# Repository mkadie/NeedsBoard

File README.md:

# T-Rex Talk — AAC Communication Device

An open-source Augmentative and Alternative Communication (AAC) device
that helps people communicate by pressing pictures on a screen. When a
picture is pressed, the device speaks a word or phrase out loud.

**No programming knowledge needed.** Teachers and parents customize
the device by editing simple text files.

*Four T-Rex Talk devices in custom 3D printed cases — touch screen and encoder variants*

<table>
<tr>
<td><br><em>Button + LCD variant</em></td>
<td><br><em>Picture button variant</em></td>
</tr>
</table>

> **Build your own!** See the [Build-a-Box photo album](https://photos.app.goo.gl/G9FtMMnnMuZ1zZxx8) for step-by-step 3D printing and assembly photos.

## Quick Start

1. **Flash CircuitPython** onto a supported device ([SETUP.md](SETUP.md))
2. **Copy the installer** to an SD card ([installer/README.md](installer/README.md))
3. **Insert SD card and reboot** — auto-configures everything
4. **Customize** menus and sounds ([GUIDE_FOR_TEACHERS.md](GUIDE_FOR_TEACHERS.md))

## Supported Devices

| Device | Screen | Input | Best For |
|--------|--------|-------|----------|
| **CYD_PLUS** | 320×240 color touch | Touch screen | Primary AAC device |
| **Fruit Jam** | 160×128 color LCD | Rotary encoder | Compact, low-power |
| **OLED Badge** | 128×32 mono OLED | Rotary encoder | Wearable, text-only |
| **Feather RP2350** | 320×240 color LCD | 8 physical buttons + encoder | Physical button access |

## Features

- **Picture-based communication** — touch or press to speak
- **Menu system** — organize vocabulary into topic boards
- **Emergency button** — instant help message on hold (~1.2 seconds)
- **Configurable** — volume, speed, sleep, encoder direction via config.txt
- **Multi-language** — bilingual support (tested with Thai/English)
- **Playback speed** — slow down speech for pre-verbal learners
- **Sleep/wake** — battery-friendly power management
- **SD card installer** — auto-detects board and configures device

## Documentation

| Document | Audience |
|----------|----------|
| [SETUP.md](SETUP.md) | Setting up a new device |
| [GUIDE_FOR_TEACHERS.md](GUIDE_FOR_TEACHERS.md) | Teachers and parents — customizing menus and sounds |
| [user_manual/USER_MANUAL.html](user_manual/USER_MANUAL.html) | End users — daily operation guide |
| [menu_system.md](menu_system.md) | Technical — menu file format reference |
| [HISTORY.md](HISTORY.md) | Project version history |
| [NOTES.md](NOTES.md) | Development notes and future plans |
| [Credits.md](Credits.md) | Contributors and acknowledgments |
Link to google docs schedule of events https://docs.google.com/document/d/1B_Ffg2c_vWS-k63qlIgnEBgbQ5qvtrQ6X7UFEZSzED0/edit?usp=sharing

## Project Structure

```
code.py                 ← Entry point
machine.py              ← Main orchestrator
hardware_config.py      ← Device variant definitions
config.txt              ← User settings (per device)
display_manager.py      ← Display drivers (ILI9341, ST7735R, SSD1306)
audio_player.py         ← MP3/WAV playback with speed control
input_manager.py        ← Touch, encoder, I2C buttons
sleep_manager.py        ← Power management
menu_parser.py          ← .menu file reader
action.py               ← Press actions (sound, image, vibrate, navigate)
config_reader.py        ← config.txt parser
storage_manager.py      ← SD card support

menus/                  ← Menu definitions (.menu files)
    images/             ← Button images
    sounds/             ← Sound files
button_sounds/          ← Base menu sounds
installer/              ← SD card auto-installer
user_manual/            ← HTML user manual with images
original_icons/         ← Source icon library
```

## Configuration (config.txt)

```
volume = 80
playback_speed = 100
sleep_timeout = 120
start_menu = base.menu
emergency_push_enabled = true
encoder_direction_flip = false
```

See [GUIDE_FOR_TEACHERS.md](GUIDE_FOR_TEACHERS.md) for all settings.

## Contributing

See [help_wanted.md](help_wanted.md) for ways to contribute:
- Software engineers
- 3D designers
- Special needs experts
- Symbol/icon designers
- Web developers

## License

MIT License — see [LICENSE](LICENSE)

## Project History

This project began in the early 1990s when Michael Kadie built two speech
boards for children with special needs.

*The original speech boards (1990s) — inspiration for T-Rex Talk*

See [HISTORY.md](HISTORY.md) for the full version history from V0.x to V3.0.

## Credits

Created by Michael Kadie. See [Credits.md](Credits.md) for full acknowledgments.

---

*T-Rex Talk: Giving a voice to those who need one.*

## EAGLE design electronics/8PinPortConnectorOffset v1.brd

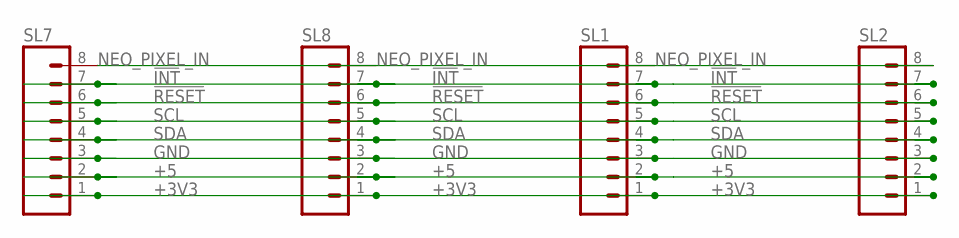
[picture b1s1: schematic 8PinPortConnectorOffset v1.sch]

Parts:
SL1, SL2, SL7, SL8: MA08; 08PA

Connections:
!INT: SL1.7, SL2.7, SL7.7, SL8.7
!RESET: SL1.6, SL2.6, SL7.6, SL8.6
+3V3: SL1.1, SL2.1, SL7.1, SL8.1
+5: SL1.2, SL2.2, SL7.2, SL8.2
GND: SL1.3, SL2.3, SL7.3, SL8.3
NEO_PIXEL_IN: SL1.8, SL2.8, SL7.8, SL8.8
SCL: SL1.5, SL2.5, SL7.5, SL8.5
SDA: SL1.4, SL2.4, SL7.4, SL8.4

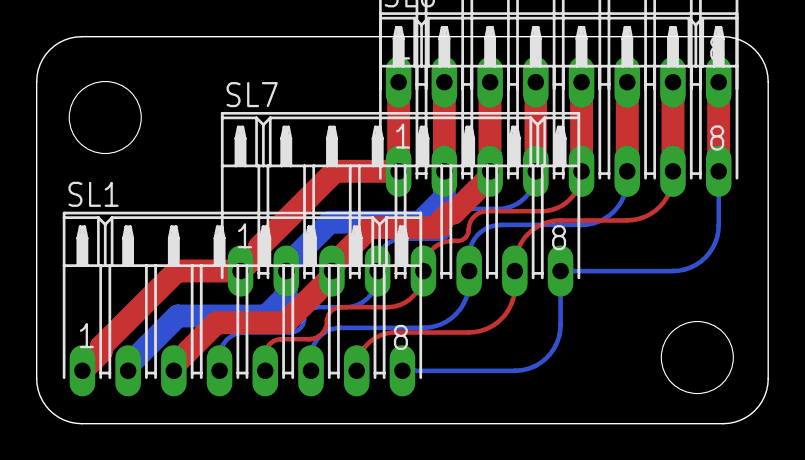
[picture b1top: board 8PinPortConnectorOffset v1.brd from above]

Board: 2 copper layers, 40.6 x 21.5 mm, 4 parts (0 on the bottom side), 8 nets.

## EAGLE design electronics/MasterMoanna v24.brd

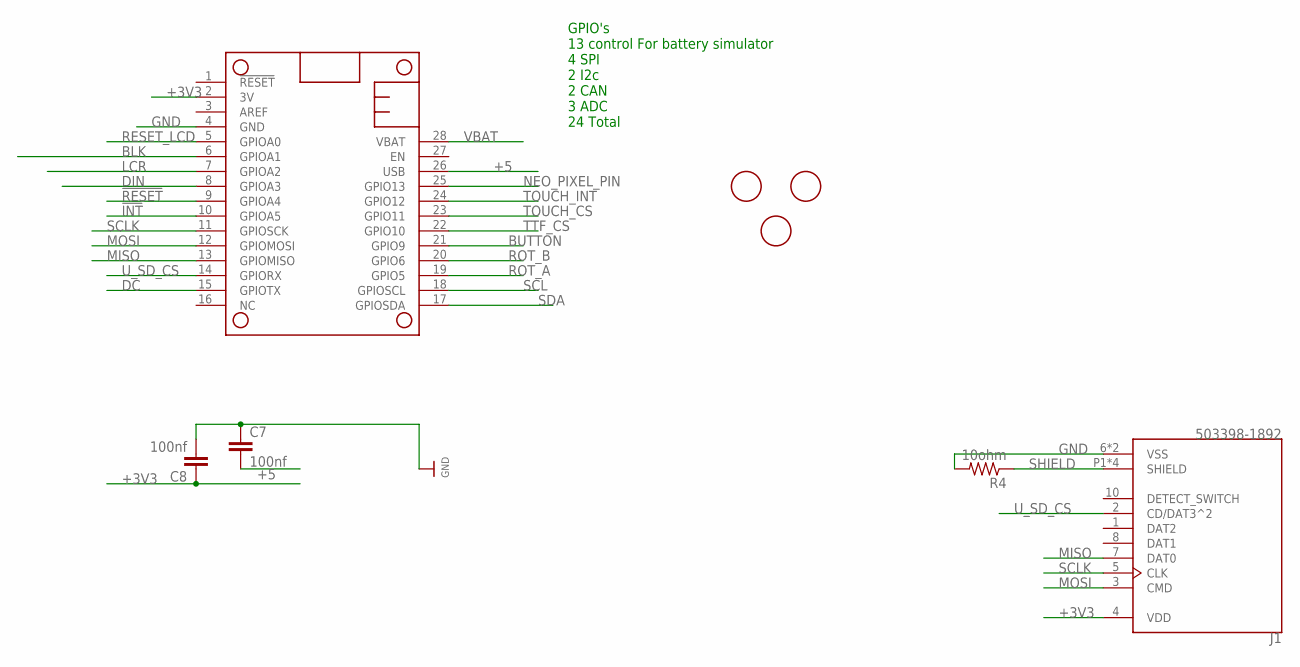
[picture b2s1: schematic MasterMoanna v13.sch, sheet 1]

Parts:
C7, C8: 100nf; C0805
FID1, FID2, FID3: FIDUCIAL; FIDUCIAL_1MM
J1: 503398-1892; MOLEX_503398-1892
MS2: FEATHERWING_NODIM; FEATHERWING_DIM
R4: 10ohm; M0805

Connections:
!INT: MS2.10 (GPIOA5); also elsewhere on the board
!RESET: MS2.9 (GPIOA4); also elsewhere on the board
+3V3: C8.1, J1.4 (VDD), MS2.2 (3V); also elsewhere on the board
+5: C7.2, MS2.26 (USB); also elsewhere on the board
BLK: MS2.6 (GPIOA1); also elsewhere on the board
BUTTON: MS2.21 (GPIO9); also elsewhere on the board
DC: MS2.15 (GPIOTX); also elsewhere on the board
DIN: MS2.8 (GPIOA3); also elsewhere on the board
GND: C7.1, C8.2, J1.6 (VSS), J1.9 (VSS), MS2.4 (GND), R4.2; also elsewhere on the board
LCR: MS2.7 (GPIOA2); also elsewhere on the board
MISO: J1.7 (DAT0), MS2.13 (GPIOMISO); also elsewhere on the board
MOSI: J1.3 (CMD), MS2.12 (GPIOMOSI); also elsewhere on the board
NEO_PIXEL_PIN: MS2.25 (GPIO13); also elsewhere on the board
RESET_LCD: MS2.5 (GPIOA0); also elsewhere on the board
ROT_A: MS2.19 (GPIO5); also elsewhere on the board
ROT_B: MS2.20 (GPIO6); also elsewhere on the board
SCL: MS2.18 (GPIOSCL); also elsewhere on the board
SCLK: J1.5 (CLK), MS2.11 (GPIOSCK); also elsewhere on the board
SDA: MS2.17 (GPIOSDA); also elsewhere on the board
SHIELD: J1.P1 (SHIELD), J1.P2 (SHIELD), J1.P3 (SHIELD), J1.P4 (SHIELD), R4.1
TOUCH_CS: MS2.23 (GPIO11); also elsewhere on the board
TOUCH_INT: MS2.24 (GPIO12); also elsewhere on the board
TTF_CS: MS2.22 (GPIO10); also elsewhere on the board
U_SD_CS: J1.2 (CD/DAT3^2), MS2.14 (GPIORX)
VBAT: MS2.28 (VBAT)

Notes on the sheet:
GPIO's 13 control For battery simulator 4 SPI 2 I2c 2 CAN 3 ADC 24 Total

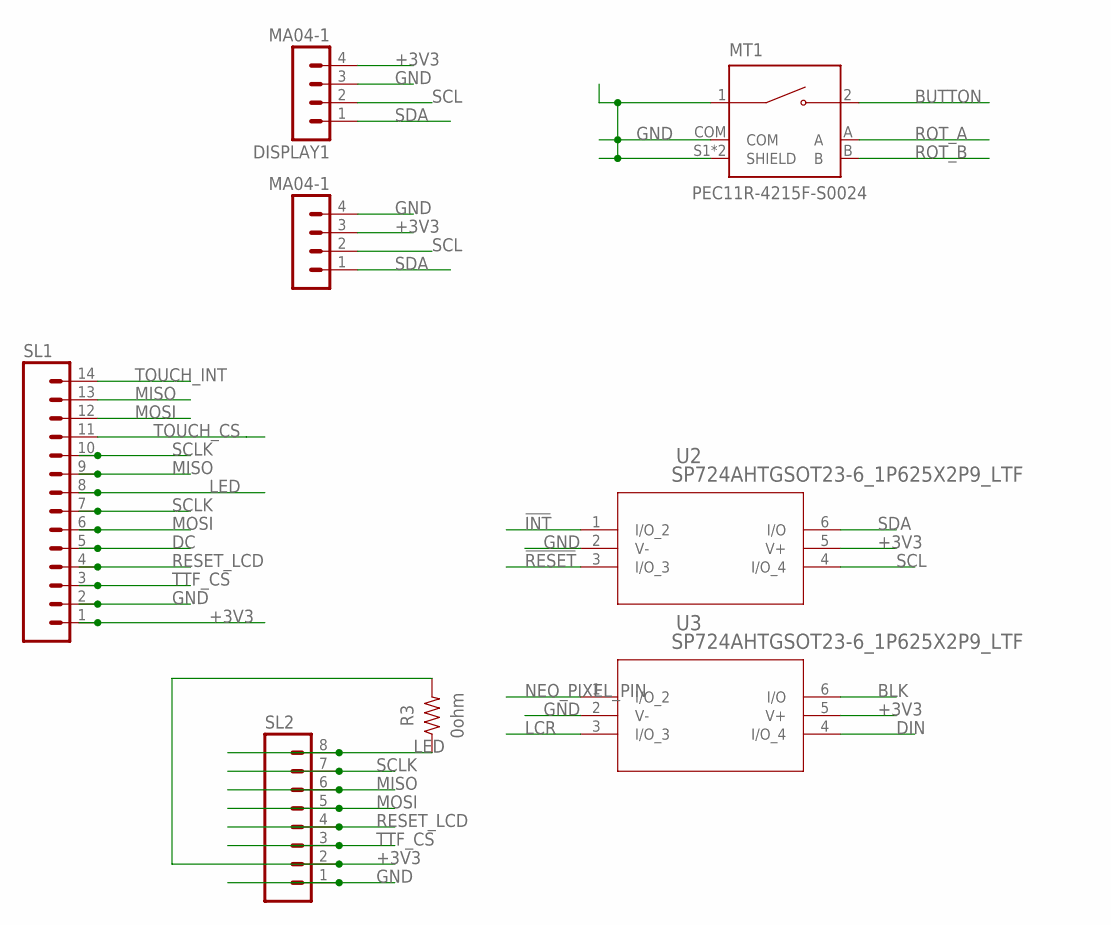
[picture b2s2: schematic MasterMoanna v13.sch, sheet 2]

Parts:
DISPLAY, DISPLAY1: MA04-1
MT1: PEC11R-4215F-S0024; XDCR_PEC11R-4215F-S0024
R3: 0ohm; RESC2012X65
SL1: MA14; 14PA
SL2: MA08; 08PA
U2, U3: SP724AHTGSOT23-6_1P625X2P9_LTF; SOT23-6_1P625X2P9_LTF

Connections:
!INT: U2.1 (I/O_2); also elsewhere on the board
!RESET: U2.3 (I/O_3); also elsewhere on the board
+3V3: DISPLAY.3 (C), DISPLAY1.4 (D), R3.2, SL1.1, SL2.2, U2.5 (V+), U3.5 (V+); also elsewhere on the board
BLK: U3.6 (I/O); also elsewhere on the board
BUTTON: MT1.2; also elsewhere on the board
DC: SL1.5; also elsewhere on the board
DIN: U3.4 (I/O_4); also elsewhere on the board
GND: DISPLAY.4 (D), DISPLAY1.3 (C), MT1.1, MT1.COM, MT1.S1 (SHIELD), MT1.S2 (SHIELD), SL1.2, SL2.1, U2.2 (V-), U3.2 (V-); also elsewhere on the board
LCR: U3.3 (I/O_3); also elsewhere on the board
LED: R3.1, SL1.8, SL2.8
MISO: SL1.9, SL1.13, SL2.6; also elsewhere on the board
MOSI: SL1.6, SL1.12, SL2.5; also elsewhere on the board
NEO_PIXEL_PIN: U3.1 (I/O_2); also elsewhere on the board
RESET_LCD: SL1.4, SL2.4; also elsewhere on the board
ROT_A: MT1.A; also elsewhere on the board
ROT_B: MT1.B; also elsewhere on the board
SCL: DISPLAY.2 (B), DISPLAY1.2 (B), U2.4 (I/O_4); also elsewhere on the board
SCLK: SL1.7, SL1.10, SL2.7; also elsewhere on the board
SDA: DISPLAY.1 (A), DISPLAY1.1 (A), U2.6 (I/O); also elsewhere on the board
TOUCH_CS: SL1.11; also elsewhere on the board
TOUCH_INT: SL1.14; also elsewhere on the board
TTF_CS: SL1.3, SL2.3; also elsewhere on the board

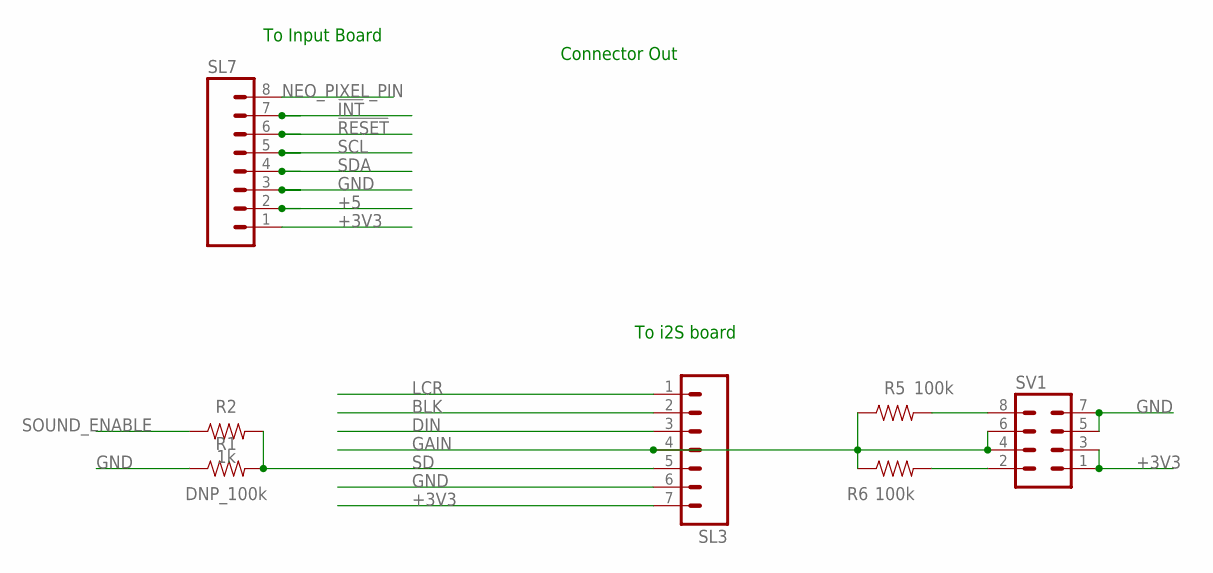
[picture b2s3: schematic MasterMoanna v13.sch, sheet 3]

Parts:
R1: DNP_100k; RESC2012X65
R2: 1k; RESC2012X65
R5, R6: 100k; RESC2012X65
SL3: MA07; 07PA
SL7: MA08; 08PA
SV1: MA04-2

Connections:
!INT: SL7.7; also elsewhere on the board
!RESET: SL7.6; also elsewhere on the board
+3V3: SL3.7, SL7.1, SV1.1, SV1.3; also elsewhere on the board
+5: SL7.2; also elsewhere on the board
BLK: SL3.2; also elsewhere on the board
DIN: SL3.3; also elsewhere on the board
GAIN: R5.1, R6.1, SL3.4, SV1.4, SV1.6
GND: R1.1, SL3.6, SL7.3, SV1.5, SV1.7; also elsewhere on the board
LCR: SL3.1; also elsewhere on the board
unnamed: R5.2, SV1.8
unnamed: R6.2, SV1.2
NEO_PIXEL_PIN: SL7.8; also elsewhere on the board
SCL: SL7.5; also elsewhere on the board
SD: R1.2, R2.2, SL3.5
SDA: SL7.4; also elsewhere on the board
SOUND_ENABLE: R2.1

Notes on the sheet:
Connector Out
To Input Board
To i2S board

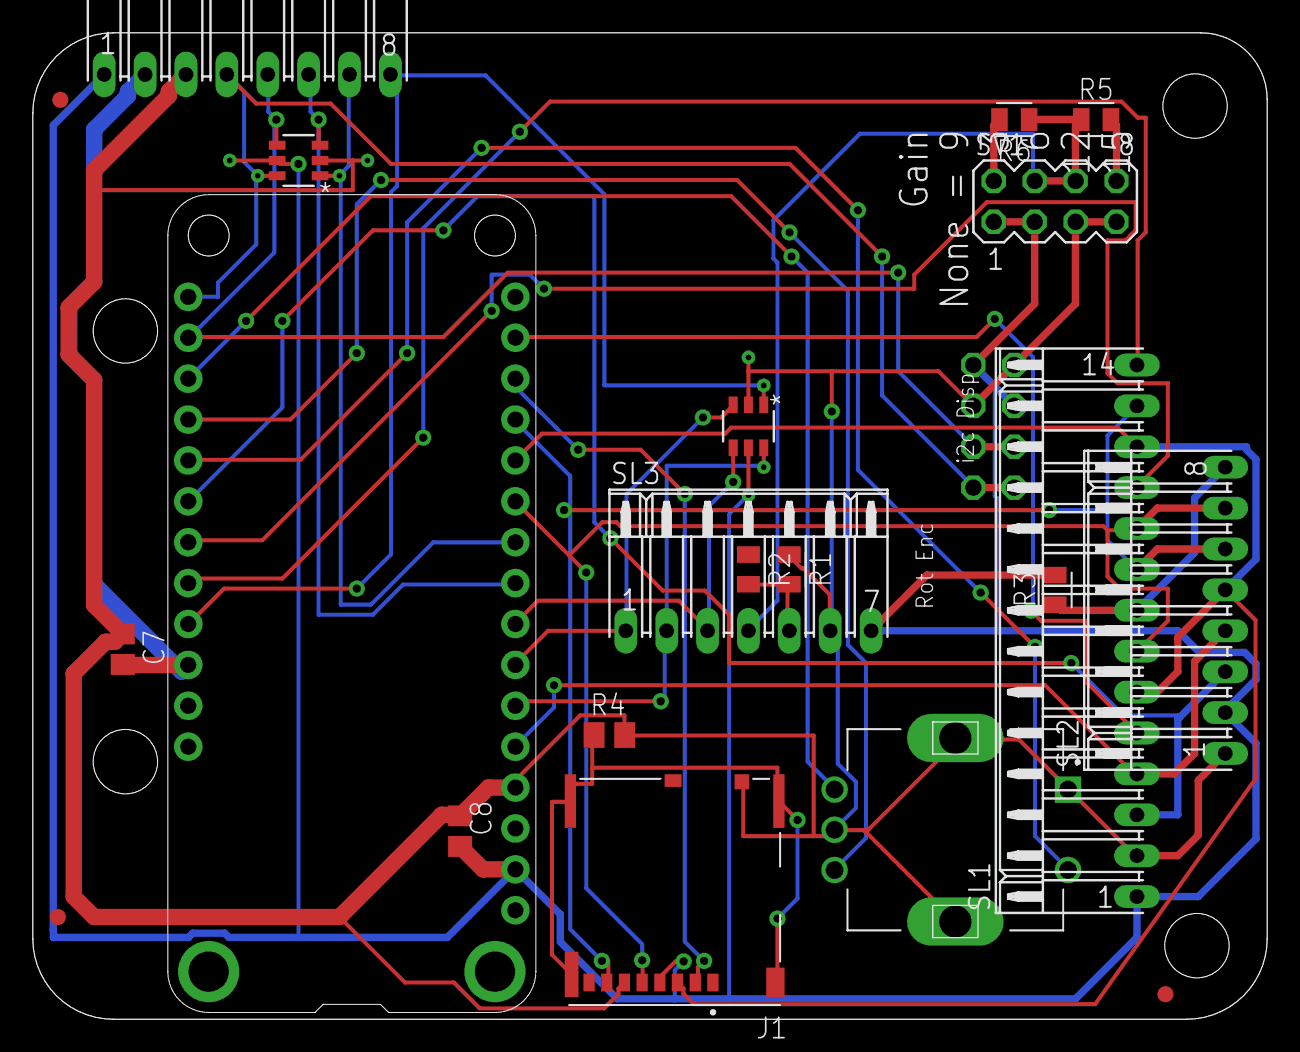
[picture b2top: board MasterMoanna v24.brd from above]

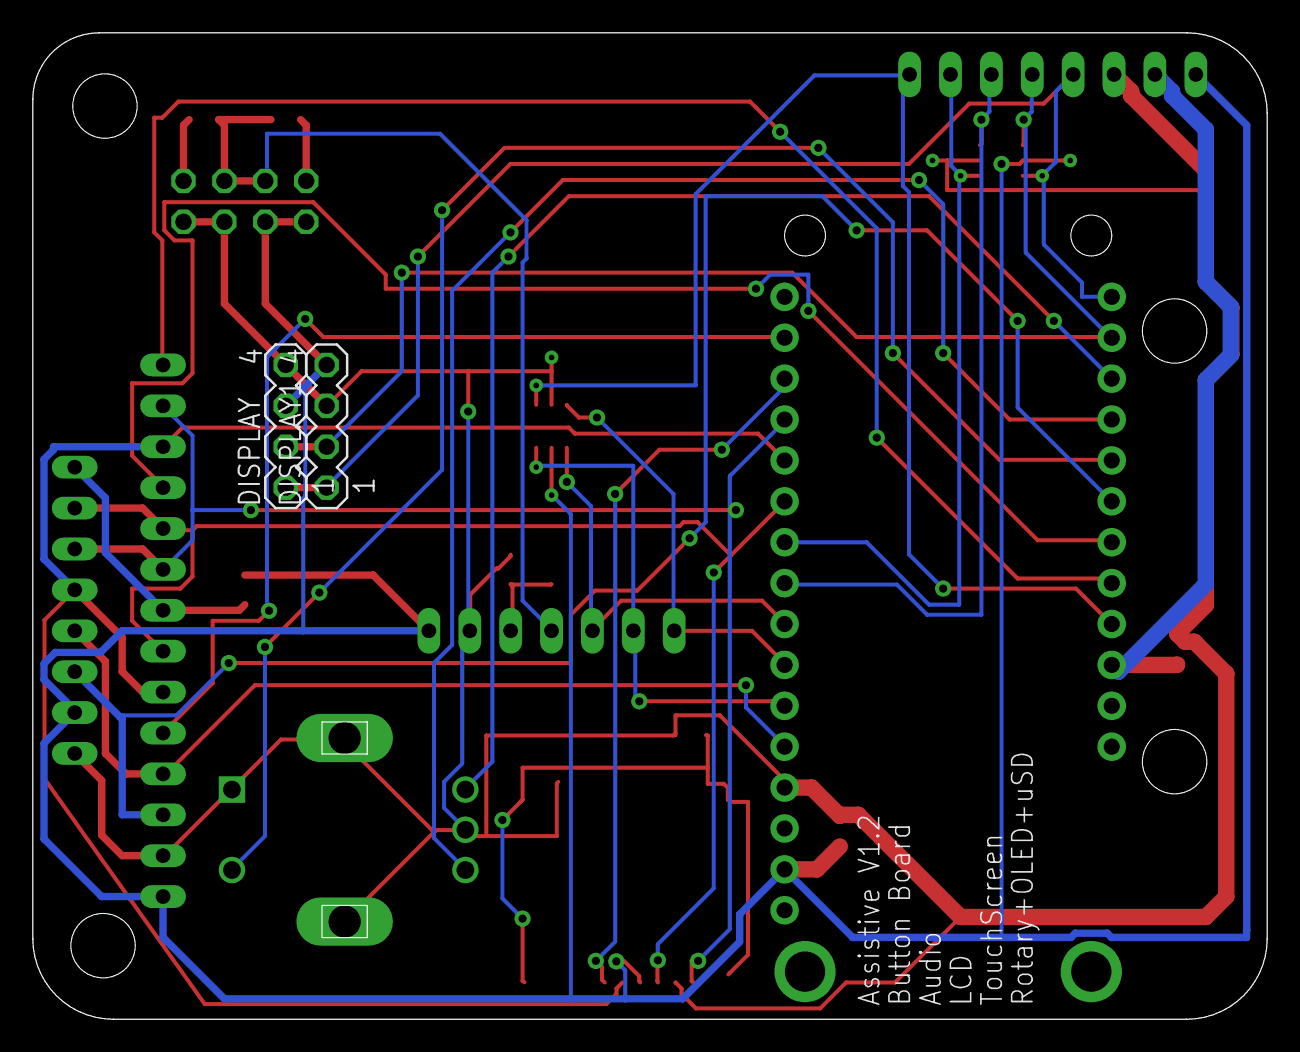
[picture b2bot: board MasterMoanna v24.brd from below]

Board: 2 copper layers, 76.7 x 61.3 mm, 23 parts (2 on the bottom side), 29 nets.

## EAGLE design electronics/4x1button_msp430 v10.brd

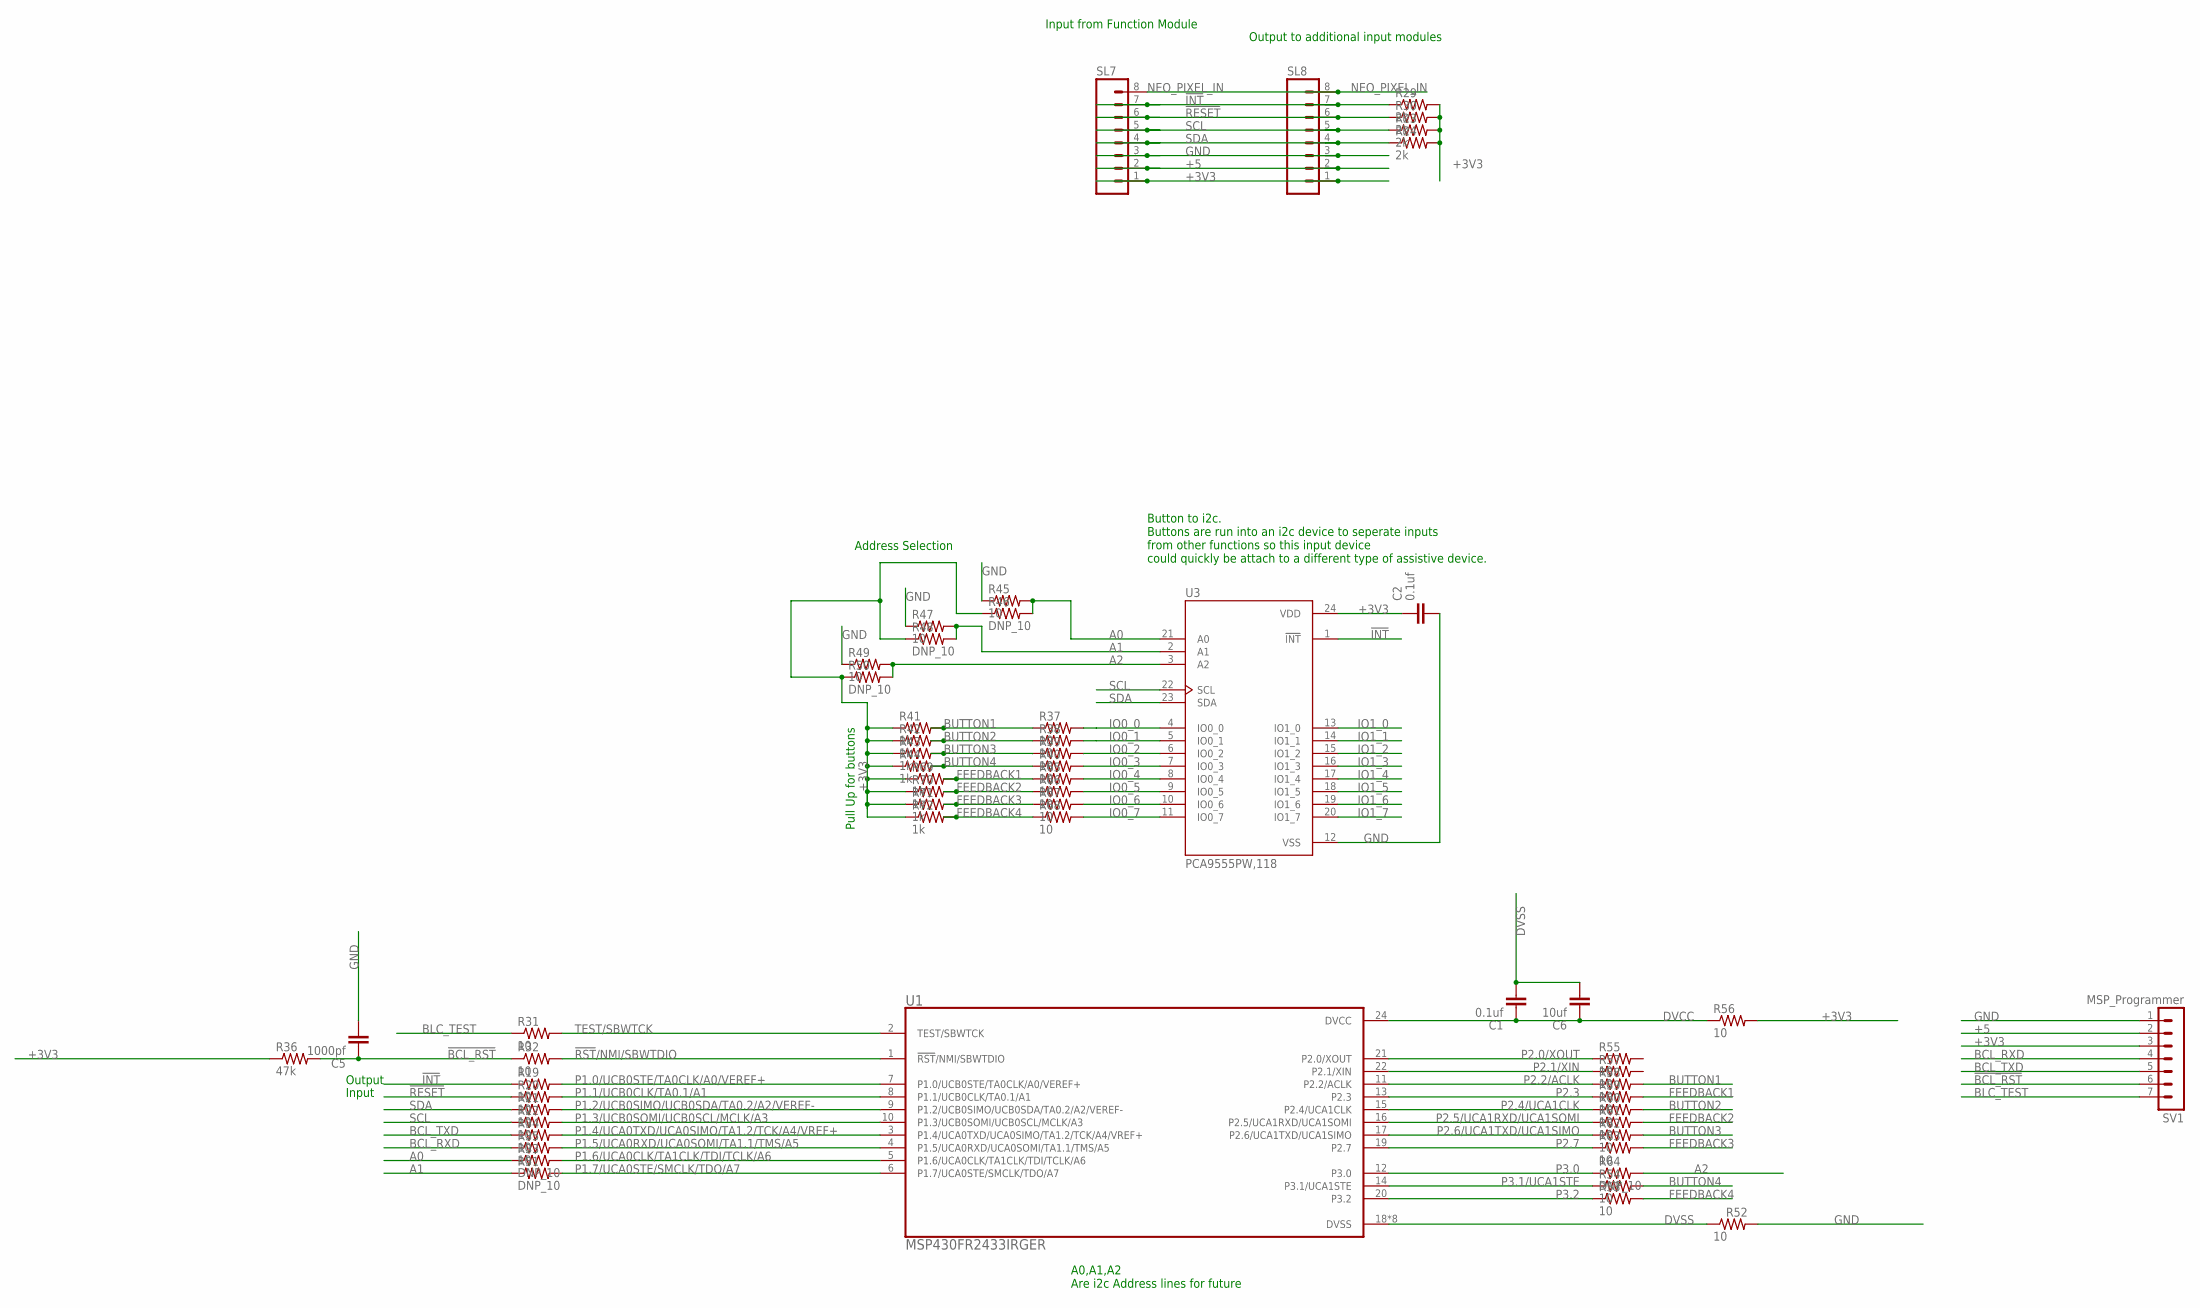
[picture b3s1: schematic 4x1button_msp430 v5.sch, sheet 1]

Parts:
C1, C2: 0.1uf; CAPC2012X110
C5: 1000pf; CAPC2012X110
C6: 10uf; CAPC2012X110
R19, R20, R21, R22, R31, R32, R34, R35, R37, R38, R39, R40, R45, R47, R49, R52, R53, R54, R55, R56, R57, R58, R59, R60, R61, R62, R63, R65, R66, R67, R68: 10; R0805
R23, R24, R29, R30: 2k; R0805
R33, R46, R48, R50, R51, R64: DNP_10; R0805
R36: 47k; R0805
R41, R42, R43, R44, R69, R70, R71, R72: 1k; R0805
SL7, SL8: MA08; 08PA
SV1: MSP_Programmer; MA07-1
U1: MSP430FR2433IRGER; QFN50P400X400X100-25N
U3: PCA9555PW,118; SOP65P640X110-24N

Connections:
!BCL_RST: C5.1, R32.1, R36.2, SV1.6
!INT: R19.1, R29.1, SL7.7, SL8.7, U3.1 (!INT)
!RESET: R20.1, R30.1, SL7.6, SL8.6
!RST!/NMI/SBWTDIO: R32.2, U1.1 (!RST!/NMI/SBWTDIO)
+3V3: C2.1, R23.2, R24.2, R29.2, R30.2, R36.1, R41.1, R42.1, R43.1, R44.1, R46.1, R48.1, R50.1, R56.2, R69.1, R70.1, R71.1, R72.1, SL7.1, SL8.1, SV1.3, U3.24 (VDD); also elsewhere on the board
+5: SL7.2, SL8.2, SV1.2; also elsewhere on the board
A0: R33.1, R45.2, R46.2, U3.21 (A0)
A1: R47.2, R48.2, R51.1, U3.2 (A1)
A2: R49.2, R50.2, R64.2, U3.3 (A2)
BCL_RXD: R35.1, SV1.4
BCL_TXD: R34.1, SV1.5
BLC_TEST: R31.1, SV1.7
BUTTON1: R37.1, R41.2, R58.2; also elsewhere on the board
BUTTON2: R38.1, R42.2, R60.2; also elsewhere on the board
BUTTON3: R39.1, R43.2, R62.2; also elsewhere on the board
BUTTON4: R40.1, R44.2, R54.2; also elsewhere on the board
DVCC: C1.1, C6.1, R56.1, U1.24 (DVCC)
DVSS: C1.2, C6.2, R52.1, U1.18 (DVSS), U1.23 (DVSS), U1.25 (DVSS), U1.26 (DVSS), U1.27 (DVSS), U1.28 (DVSS), U1.29 (DVSS), U1.30 (DVSS)
FEEDBACK1: R59.2, R65.1, R69.2; also elsewhere on the board
FEEDBACK2: R61.2, R66.1, R70.2; also elsewhere on the board
FEEDBACK3: R63.2, R67.1, R71.2; also elsewhere on the board
FEEDBACK4: R53.2, R68.1, R72.2; also elsewhere on the board
GND: C2.2, C5.2, R45.1, R47.1, R49.1, R52.2, SL7.3, SL8.3, SV1.1, U3.12 (VSS); also elsewhere on the board
IO0_0: R37.2, U3.4 (IO0_0)
IO0_1: R38.2, U3.5 (IO0_1)
IO0_2: R39.2, U3.6 (IO0_2)
IO0_3: R40.2, U3.7 (IO0_3)
IO0_4: R65.2, U3.8 (IO0_4)
IO0_5: R66.2, U3.9 (IO0_5)
IO0_6: R67.2, U3.10 (IO0_6)
IO0_7: R68.2, U3.11 (IO0_7)
IO1_0: U3.13 (IO1_0)
IO1_1: U3.14 (IO1_1)
IO1_2: U3.15 (IO1_2)
IO1_3: U3.16 (IO1_3)
IO1_4: U3.17 (IO1_4)
IO1_5: U3.18 (IO1_5)
IO1_6: U3.19 (IO1_6)
IO1_7: U3.20 (IO1_7)
NEO_PIXEL_IN: SL7.8, SL8.8; also elsewhere on the board
P1.0/UCB0STE/TA0CLK/A0/VEREF+: R19.2, U1.7 (P1.0/UCB0STE/TA0CLK/A0/VEREF+)
P1.1/UCB0CLK/TA0.1/A1: R20.2, U1.8 (P1.1/UCB0CLK/TA0.1/A1)
P1.2/UCB0SIMO/UCB0SDA/TA0.2/A2/VEREF-: R21.2, U1.9 (P1.2/UCB0SIMO/UCB0SDA/TA0.2/A2/VEREF-)
P1.3/UCB0SOMI/UCB0SCL/MCLK/A3: R22.2, U1.10 (P1.3/UCB0SOMI/UCB0SCL/MCLK/A3)
P1.4/UCA0TXD/UCA0SIMO/TA1.2/TCK/A4/VREF+: R34.2, U1.3 (P1.4/UCA0TXD/UCA0SIMO/TA1.2/TCK/A4/VREF+)
P1.5/UCA0RXD/UCA0SOMI/TA1.1/TMS/A5: R35.2, U1.4 (P1.5/UCA0RXD/UCA0SOMI/TA1.1/TMS/A5)
P1.6/UCA0CLK/TA1CLK/TDI/TCLK/A6: R33.2, U1.5 (P1.6/UCA0CLK/TA1CLK/TDI/TCLK/A6)
P1.7/UCA0STE/SMCLK/TDO/A7: R51.2, U1.6 (P1.7/UCA0STE/SMCLK/TDO/A7)
P2.0/XOUT: R55.1, U1.21 (P2.0/XOUT)
P2.1/XIN: R57.1, U1.22 (P2.1/XIN)
P2.2/ACLK: R58.1, U1.11 (P2.2/ACLK)
P2.3: R59.1, U1.13 (P2.3)
P2.4/UCA1CLK: R60.1, U1.15 (P2.4/UCA1CLK)
P2.5/UCA1RXD/UCA1SOMI: R61.1, U1.16 (P2.5/UCA1RXD/UCA1SOMI)
P2.6/UCA1TXD/UCA1SIMO: R62.1, U1.17 (P2.6/UCA1TXD/UCA1SIMO)
P2.7: R63.1, U1.19 (P2.7)
P3.0: R64.1, U1.12 (P3.0)
P3.1/UCA1STE: R54.1, U1.14 (P3.1/UCA1STE)
P3.2: R53.1, U1.20 (P3.2)
SCL: R22.1, R23.1, SL7.5, SL8.5, U3.22 (SCL)
SDA: R21.1, R24.1, SL7.4, SL8.4, U3.23 (SDA)
TEST/SBWTCK: R31.2, U1.2 (TEST/SBWTCK)

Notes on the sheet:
Pull Up for buttons
Address Selection
Button to i2c. Buttons are run into an i2c device to seperate inputs from other functions so this input device could quickly be attach to a different type of assistive device.
Input from Function Module
Output to additional input modules
Output
Input
A0,A1,A2 Are i2c Address lines for future

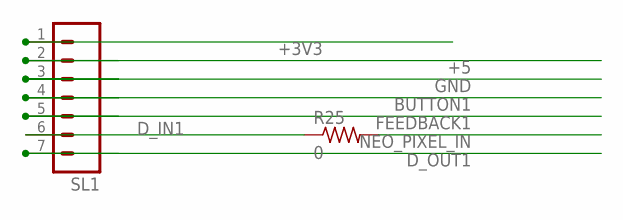
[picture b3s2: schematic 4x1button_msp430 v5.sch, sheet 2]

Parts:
R25: 0; R0805
SL1: MA07; 07PA

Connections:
+3V3: SL1.1; also elsewhere on the board
+5: SL1.2; also elsewhere on the board
BUTTON1: SL1.4; also elsewhere on the board
D_IN1: R25.1, SL1.6
D_OUT1: SL1.7; also elsewhere on the board
FEEDBACK1: SL1.5; also elsewhere on the board
GND: SL1.3; also elsewhere on the board
NEO_PIXEL_IN: R25.2; also elsewhere on the board

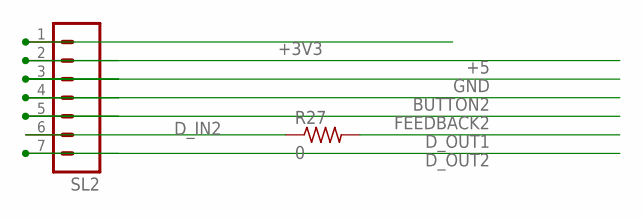
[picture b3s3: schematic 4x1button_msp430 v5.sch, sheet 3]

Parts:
R27: 0; R0805
SL2: MA07; 07PA

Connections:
+3V3: SL2.1; also elsewhere on the board
+5: SL2.2; also elsewhere on the board
BUTTON2: SL2.4; also elsewhere on the board
D_IN2: R27.1, SL2.6
D_OUT1: R27.2; also elsewhere on the board
D_OUT2: SL2.7; also elsewhere on the board
FEEDBACK2: SL2.5; also elsewhere on the board
GND: SL2.3; also elsewhere on the board

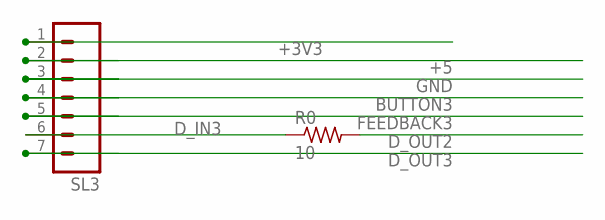
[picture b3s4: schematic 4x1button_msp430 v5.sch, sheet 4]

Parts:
R0: 10; R0805
SL3: MA07; 07PA

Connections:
+3V3: SL3.1; also elsewhere on the board
+5: SL3.2; also elsewhere on the board
BUTTON3: SL3.4; also elsewhere on the board
D_IN3: R0.1, SL3.6
D_OUT2: R0.2; also elsewhere on the board
D_OUT3: SL3.7; also elsewhere on the board
FEEDBACK3: SL3.5; also elsewhere on the board
GND: SL3.3; also elsewhere on the board

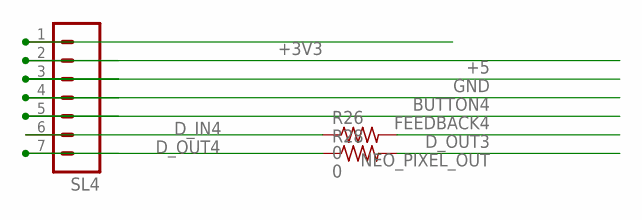
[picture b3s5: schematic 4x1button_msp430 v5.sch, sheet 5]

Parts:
R26, R28: 0; R0805
SL4: MA07; 07PA

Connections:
+3V3: SL4.1; also elsewhere on the board
+5: SL4.2; also elsewhere on the board
BUTTON4: SL4.4; also elsewhere on the board
D_IN4: R26.1, SL4.6
D_OUT3: R26.2; also elsewhere on the board
D_OUT4: R28.1, SL4.7
FEEDBACK4: SL4.5; also elsewhere on the board
GND: SL4.3; also elsewhere on the board
NEO_PIXEL_OUT: R28.2

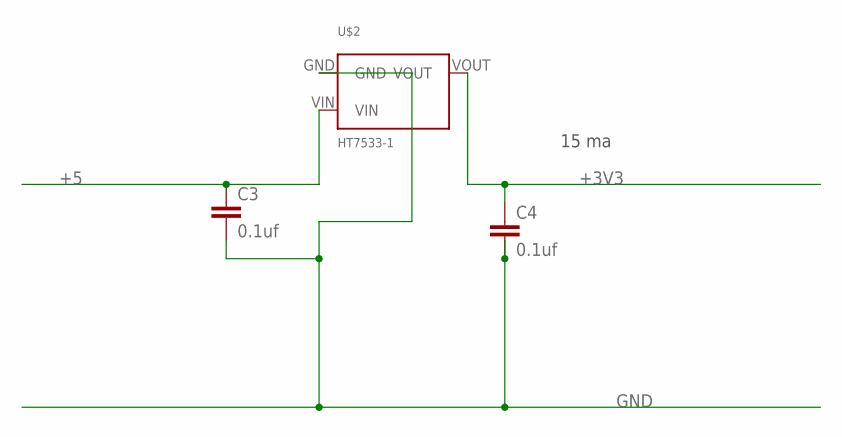
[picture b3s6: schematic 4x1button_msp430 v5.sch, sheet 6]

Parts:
C3, C4: 0.1uf; C0805
U$2: HT7533-1; HT7750-1

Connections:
+3V3: C4.1, U$2.VOUT; also elsewhere on the board
+5: C3.1, U$2.VIN; also elsewhere on the board
GND: C3.2, C4.2, U$2.GND; also elsewhere on the board

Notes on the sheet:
15 ma

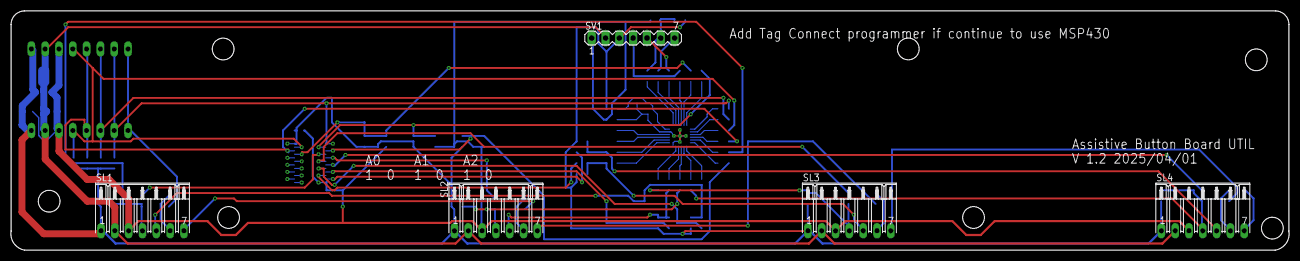
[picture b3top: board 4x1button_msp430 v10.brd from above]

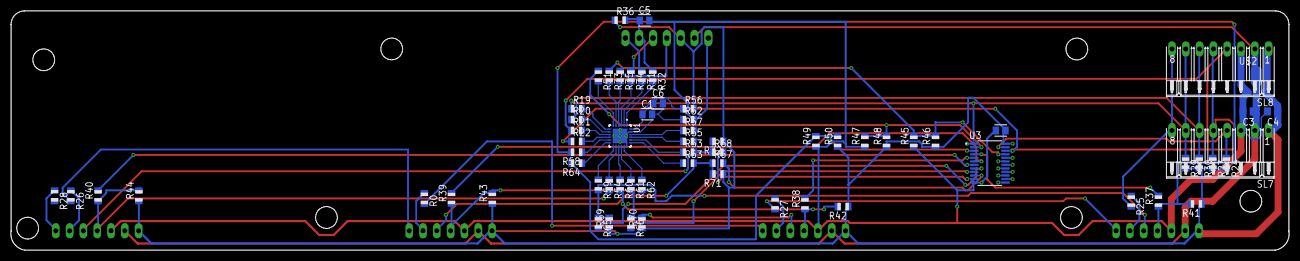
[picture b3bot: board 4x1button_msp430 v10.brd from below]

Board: 2 copper layers, 235.1 x 44.0 mm, 71 parts (66 on the bottom side), 62 nets.

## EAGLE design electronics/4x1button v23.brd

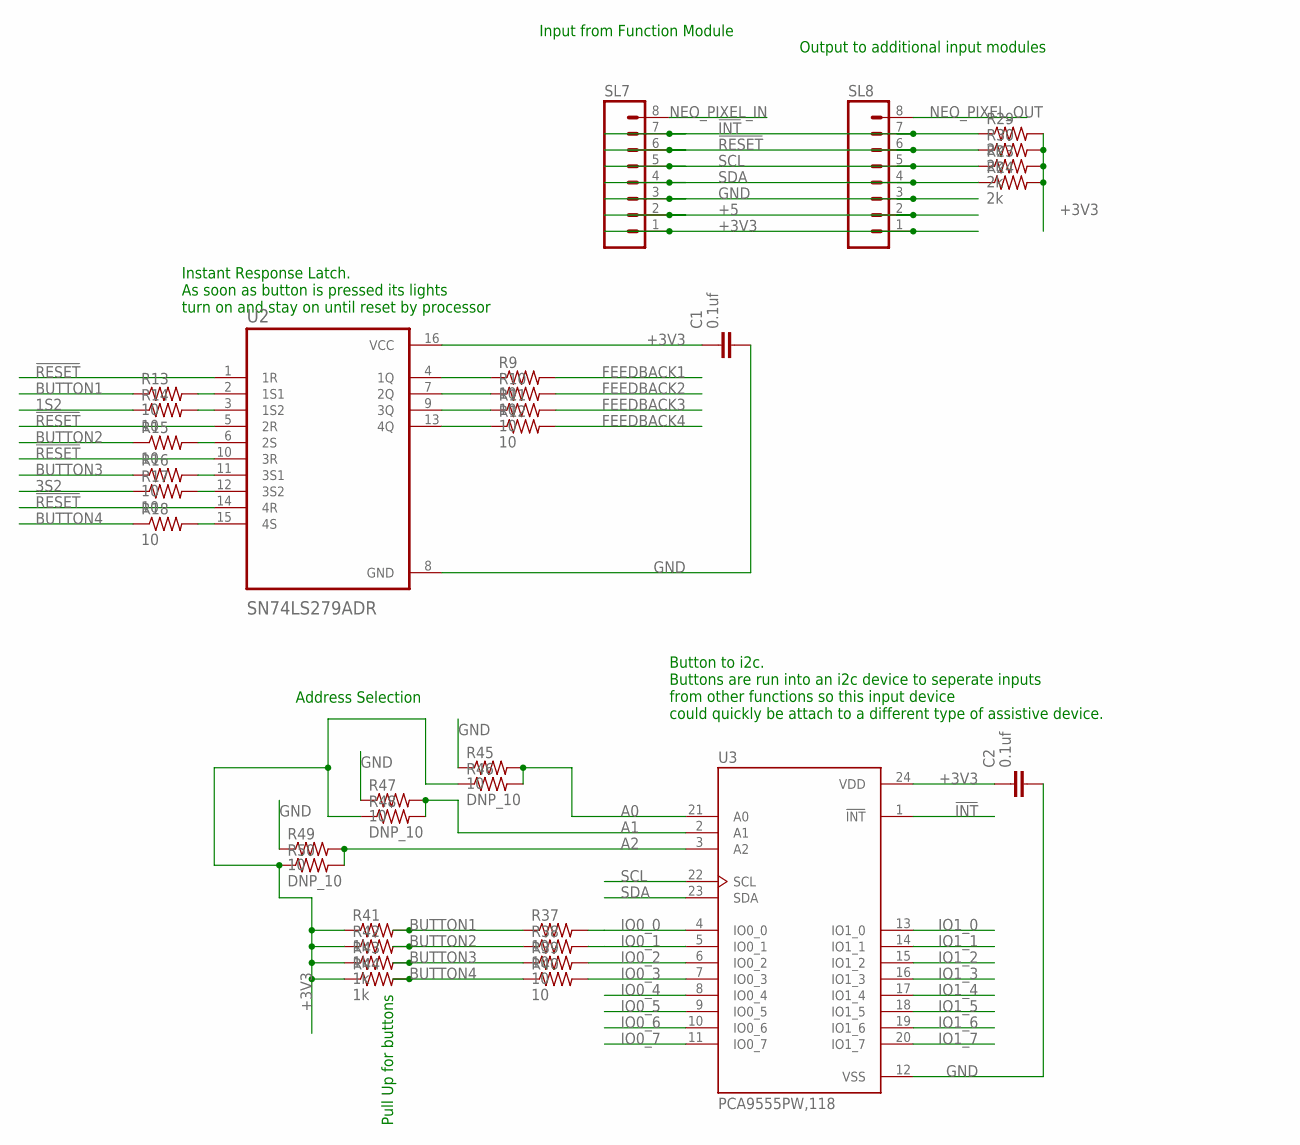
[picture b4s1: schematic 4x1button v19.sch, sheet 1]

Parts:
C1, C2: 0.1uf; CAPC2012X110
R9, R10, R11, R12, R13, R14, R15, R16, R17, R18, R37, R38, R39, R40, R45, R47, R49: 10; R0805
R23, R24, R29, R30: 2k; R0805
R41, R42, R43, R44: 1k; R0805
R46, R48, R50: DNP_10; R0805
SL7, SL8: MA08; 08PA
U2: SN74LS279ADR; SOIC127P600X175-16N
U3: PCA9555PW,118; SOP65P640X110-24N

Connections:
1S2: R14.1
3S2: R17.1
!INT: R29.1, SL7.7, SL8.7, U3.1 (!INT)
!RESET: R30.1, SL7.6, SL8.6, U2.1 (1R), U2.5 (2R), U2.10 (3R), U2.14 (4R)
+3V3: C1.1, C2.1, R23.2, R24.2, R29.2, R30.2, R41.1, R42.1, R43.1, R44.1, R46.1, R48.1, R50.1, SL7.1, SL8.1, U2.16 (VCC), U3.24 (VDD); also elsewhere on the board
+5: SL7.2, SL8.2; also elsewhere on the board
A0: R45.2, R46.2, U3.21 (A0)
A1: R47.2, R48.2, U3.2 (A1)
A2: R49.2, R50.2, U3.3 (A2)
BUTTON1: R13.1, R37.1, R41.2; also elsewhere on the board
BUTTON2: R15.1, R38.1, R42.2; also elsewhere on the board
BUTTON3: R16.1, R39.1, R43.2; also elsewhere on the board
BUTTON4: R18.1, R40.1, R44.2; also elsewhere on the board
FEEDBACK1: R9.2; also elsewhere on the board
FEEDBACK2: R10.2; also elsewhere on the board
FEEDBACK3: R11.2; also elsewhere on the board
FEEDBACK4: R12.2; also elsewhere on the board
GND: C1.2, C2.2, R45.1, R47.1, R49.1, SL7.3, SL8.3, U2.8 (GND), U3.12 (VSS); also elsewhere on the board
IO0_0: R37.2, U3.4 (IO0_0)
IO0_1: R38.2, U3.5 (IO0_1)
IO0_2: R39.2, U3.6 (IO0_2)
IO0_3: R40.2, U3.7 (IO0_3)
IO0_4: U3.8 (IO0_4)
IO0_5: U3.9 (IO0_5)
IO0_6: U3.10 (IO0_6)
IO0_7: U3.11 (IO0_7)
IO1_0: U3.13 (IO1_0)
IO1_1: U3.14 (IO1_1)
IO1_2: U3.15 (IO1_2)
IO1_3: U3.16 (IO1_3)
IO1_4: U3.17 (IO1_4)
IO1_5: U3.18 (IO1_5)
IO1_6: U3.19 (IO1_6)
IO1_7: U3.20 (IO1_7)
unnamed: R9.1, U2.4 (1Q)
unnamed: R10.1, U2.7 (2Q)
unnamed: R11.1, U2.9 (3Q)
unnamed: R12.1, U2.13 (4Q)
unnamed: R13.2, U2.2 (1S1)
unnamed: R14.2, U2.3 (1S2)
unnamed: R15.2, U2.6 (2S)
unnamed: R16.2, U2.11 (3S1)
unnamed: R17.2, U2.12 (3S2)
unnamed: R18.2, U2.15 (4S)
NEO_PIXEL_IN: SL7.8; also elsewhere on the board
NEO_PIXEL_OUT: SL8.8; also elsewhere on the board
SCL: R23.1, SL7.5, SL8.5, U3.22 (SCL)
SDA: R24.1, SL7.4, SL8.4, U3.23 (SDA)

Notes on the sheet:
Pull Up for buttons
Address Selection
Instant Response Latch. As soon as button is pressed its lights turn on and stay on until reset by processor
Button to i2c. Buttons are run into an i2c device to seperate inputs from other functions so this input device could quickly be attach to a different type of assistive device.
Input from Function Module
Output to additional input modules

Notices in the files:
parts and their libraries:
microbuilder: This work is placed in the public domain, and may be freely used for commercial and non-commercial work with the following conditions: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
2022-12-15_20-19-59_Library: COPYRIGHT: Copyright (C) 2022 Ultra Librarian. All rights reserved.
